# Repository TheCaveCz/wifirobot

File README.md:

# WiFi robot

ESP8266 chip on Wemos D1 mini module that is driving two DC geared motors using L293D chip. One WS2812 led for status, one tact switch for reset. Possibility of extending functionality via I2C bus.
Firmware contains Blynk platform integration for mobile app control. Can also be controlled using UDP packets.

More resources:
* [3D prints](stl)
* Firmware
  * [Original](firmware/robot) - uses [Arduino core for ESP8266](https://github.com/esp8266/Arduino), using [Blynk](https://blynk.cc) platform
  * [Tester](firmware/robot-test) - testing sketch
* [Hardware assembly](pictures)
* [PCB drawings](board) - created in EAGLE 9.2

## Setup

### On your computer

* Install [Arduino core for ESP8266](https://github.com/esp8266/Arduino#installing-with-boards-manager) - **use version 2.4.2 or above**
* Install the [Blynk Arduino library](http://help.blynk.cc/getting-started-library-auth-token-code-examples/how-to-install-blynk-library-for-arduino)
* Install the [WiFi Manager library](https://github.com/tzapu/WiFiManager)
* Compile and upload the [firmware](firmware/robot)

### On your mobile phone

* Install [Blynk app](https://www.blynk.cc/getting-started/)
* Create account or log in
* Create new empty project in Blynk App
* Copy auth token from the app or your email
* Connect to the robot AP
* Wait for WiFi login popup (or use browser and navigate to `http://192.168.4.1`)
* Enter WiFi credentials and auth token
* Setup the Blynk project (see next section)

### Reconfiguring or resetting robot

* Hold button until status LED lights up with violet color
* Connect to the robot AP
* Wait for WiFi login popup (or use browser and navigate to `http://192.168.4.1`)
* Enter WiFi credentials and auth token

## Blynk project

Total required energy: 1200

### Components

* Joystick
* Button
* zeRGBa
* Level H

Recommended layout:

### Component settings

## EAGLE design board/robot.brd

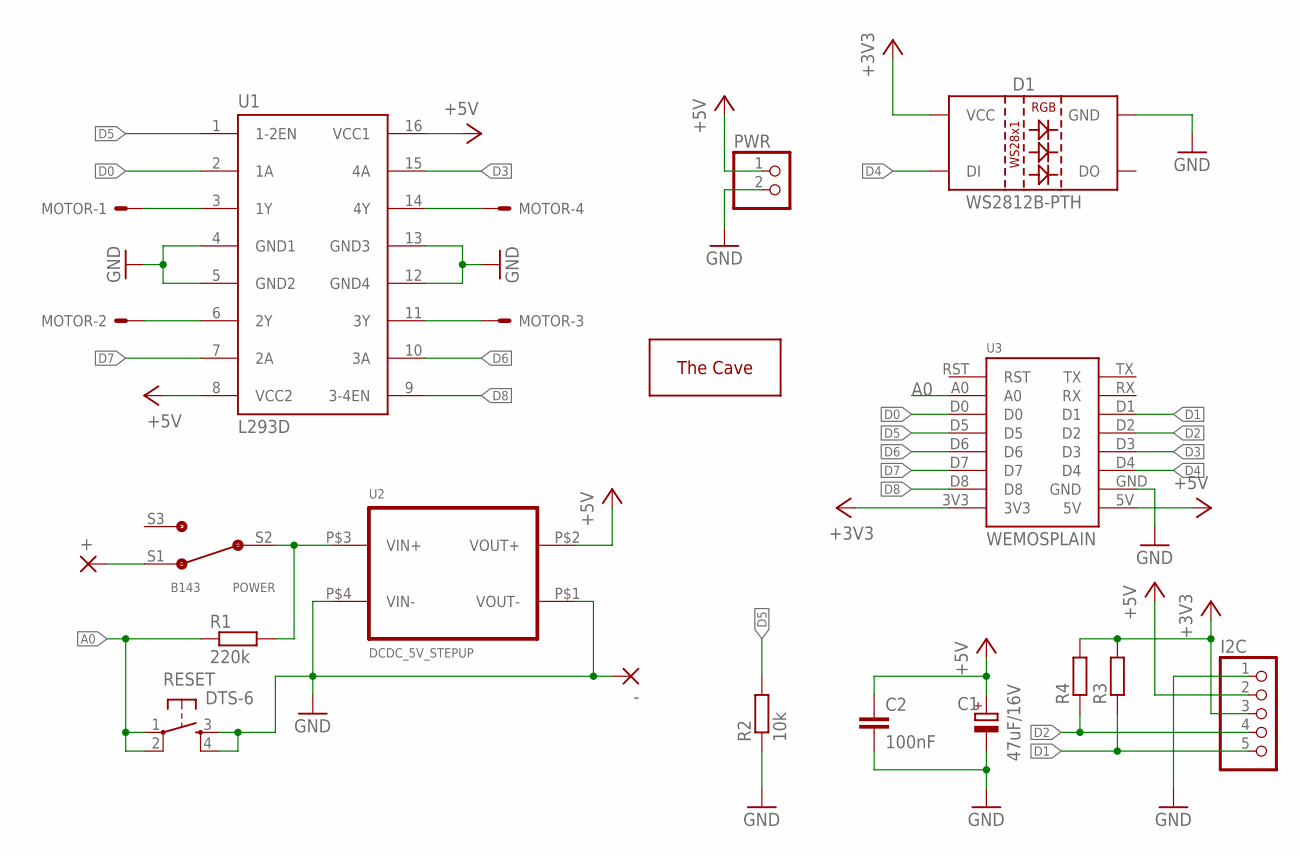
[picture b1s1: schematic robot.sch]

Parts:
+: 2,54/0,8
-: 2,54/0,8
C1: 47uF/16V; E2,5-7
C2: 100nF; C025-025X050
D1: WS2812B-PTH; WS2812B-PTH-KIT
I2C: PINHD-1X5; 1X05
MOTOR: JST-XH-04-PIN-LONG-PAD; JST-XH-04-PACKAGE-LONG-PAD
POWER: B143
PWR: PINHD-1X2; 1X02
R1: 220k; 0204/5
R2: 10k; 0204/5
R3, R4: R-EU_R0805; R0805
RESET: DTS-6
U1: L293D; DIL16
U2: DCDC_5V_STEPUP
U3: WEMOSPLAIN; WEMOS-PLAIN
U$1: THECAVE_LOGO_NEW_TOP_SMALL; NEW_LOGO_SMALL_TOP

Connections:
+3V3: D1.3-VCC (VCC), I2C.3, R3.2, R4.2, U3.3V3
+5V: C1.+, C2.1, I2C.2, PWR.1, U1.8 (VCC2), U1.16 (VCC1), U2.P$2 (VOUT+), U3.5V
A0: R1.1, RESET.1, RESET.2, U3.A0
D0: U1.2 (1A), U3.D0
D1: I2C.5, R3.1, U3.D1
D2: I2C.4, R4.1, U3.D2
D3: U1.15 (4A), U3.D3
D4: D1.1-IN (DI), U3.D4
D5: R2.2, U1.1 (1-2EN), U3.D5
D6: U1.10 (3A), U3.D6
D7: U1.7 (2A), U3.D7
D8: U1.9 (3-4EN), U3.D8
GND: -.1, C1.-, C2.2, D1.2-GND (GND), I2C.1, PWR.2, R2.1, RESET.3, RESET.4, U1.4 (GND1), U1.5 (GND2), U1.12 (GND4), U1.13 (GND3), U2.P$1 (VOUT-), U2.P$4 (VIN-), U3.GND
unnamed: MOTOR.1, U1.3 (1Y)
unnamed: MOTOR.2, U1.6 (2Y)
unnamed: MOTOR.3, U1.11 (3Y)
unnamed: MOTOR.4, U1.14 (4Y)
unnamed: POWER.S2 (COM), R1.2, U2.P$3 (VIN+)
unnamed: +.1, POWER.S1

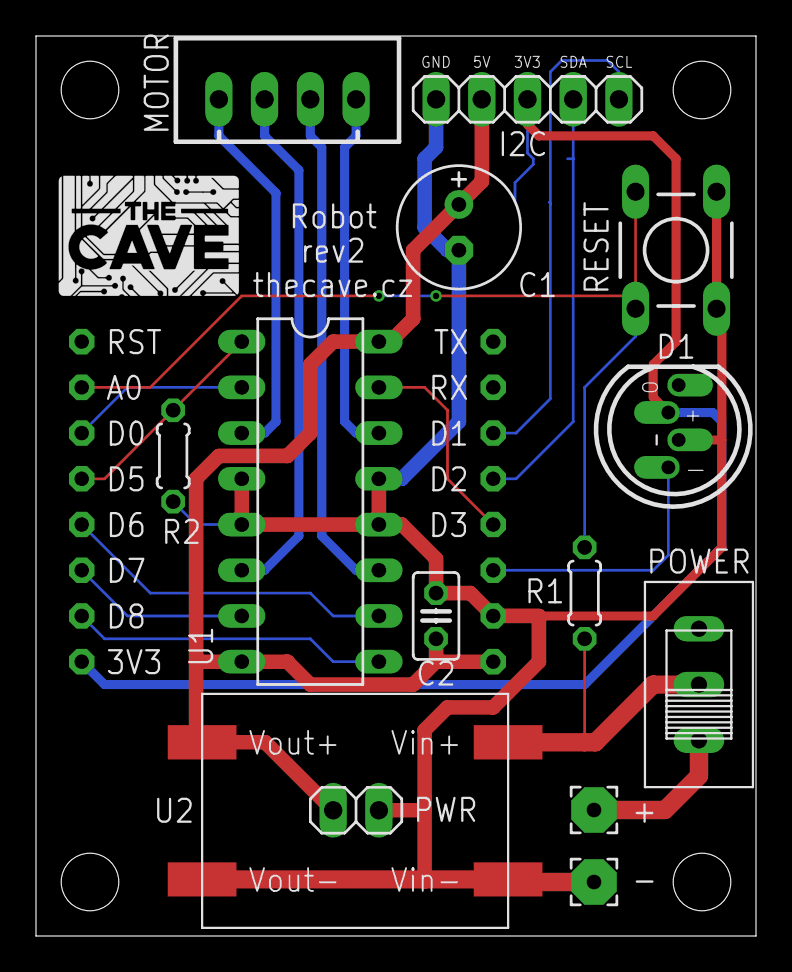
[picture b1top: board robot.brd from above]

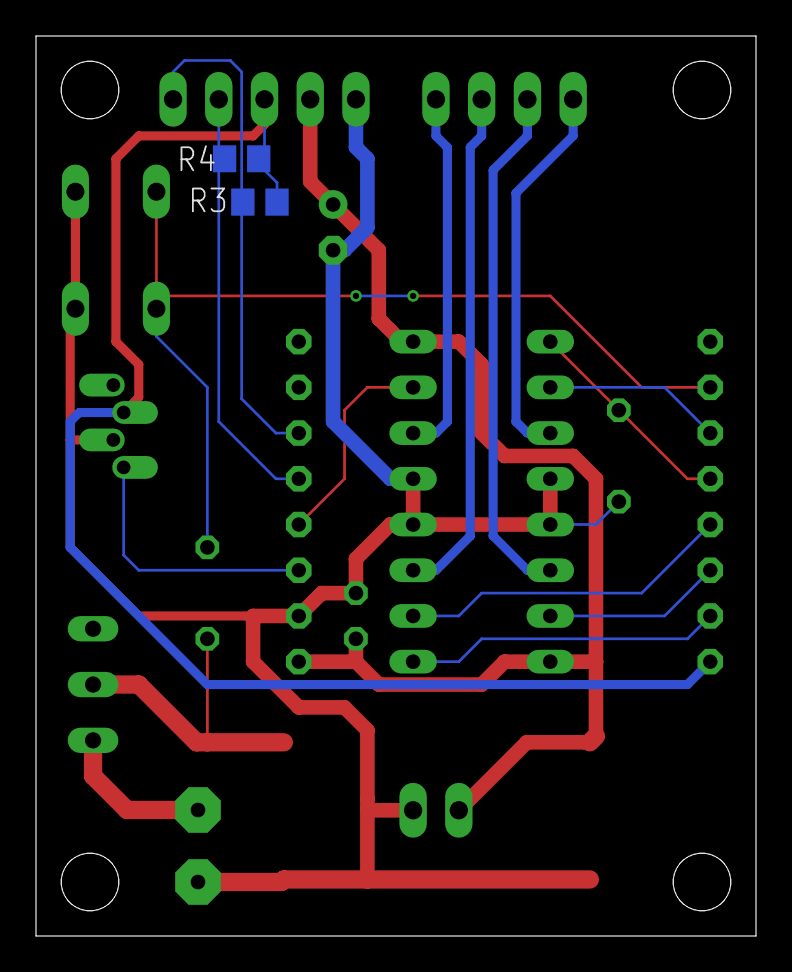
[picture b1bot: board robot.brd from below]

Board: 2 copper layers, 40.0 x 50.0 mm, 18 parts (2 on the bottom side), 19 nets.

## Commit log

2019-04-03 Add board and dxf drawing
2019-04-03 Add prints
2019-04-03 Add firmware
2019-04-10 Clean up firmware
2019-04-11 Add capacitor values
2019-04-11 Add pictures
2019-04-11 Fix space char in picture names
2019-04-11 Add main readme
2019-04-11 Reorder blynk variables
2019-04-11 Add blynk section to readme
2019-04-11 Fix typo in readme
2019-04-11 Add more blynk stuff to readme
2019-04-11 Add test firmware
2019-04-11 Add motor speed pins
2019-04-11 Final adjustments
2019-08-06 [FW] Add brake pin
